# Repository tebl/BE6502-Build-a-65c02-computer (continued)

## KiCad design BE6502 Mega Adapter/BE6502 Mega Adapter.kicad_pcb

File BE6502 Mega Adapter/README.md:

[Ben Eater](https://eater.net/) has been a huge inspiration for many getting into building computers using basic electronic building blocks, his [videos](https://www.youtube.com/user/eaterbc) are truly excellent and it is no wonder he's often referred to as the Bob Ross of Breadboards! His latest project is [building a 6502 computer](https://eater.net/6502) on a breadboard, a video series that I'm sure will also inspire a lot of new users to the art of building stuff with the 6502! Check out the main [README](https://github.com/tebl/BE6502) for an overview of all the modules available to the BE6502 computer.

## Arduino Mega 2560-shield and Backplane
During the initial videos, Ben Eater shows how an Arduino Mega 2560 can be used when debugging or even seeking to understand how a 6502 computer works. This is done by connecting up the address/data busses as well as some of the control signals (R/W and the clock), the values are then printed every clock pulse.

That's a lot of wires and I don't have that kind of patience, so I designed it as an Arduino Mega 2560-shield that doubles up as a two (or three) slot backplane. You plug the SBC-module into one of them, then you can use the other for whatever expansion module you want to try out with the system. The third and outer set of pins can be installed as slot in the same manner, but I opted to install straight header pins here instead - that way I can use some female to male dupont wires and easily run them as needed over to a breadboard.

I've adapted the Arduino sketch created by Ben Eater, mostly I've just changed a few minor things to have them just like I would like them to be - I've also added all of the other BE6502-backplane signals available since they have all been mapped over to the Arduino Mega 2560. What's particularly awesome about that is that you can program the Arduino Mega to manually control the signalling without the SBC-module present, meaning that you now have the added ability to test out expansion module logic step by step.

For more information about using the sketch to analyze the computer while it is running as well as a few annotations that should help make the data streaming into the console more understandable, see [6502-monitor](https://github.com/tebl/BE6502/tree/master/software/arduino/6502-monitor) within the software-section of the project. Arduino console with the reset vector highlighted in yellow can be seen below as an example of output.

## Jumpers
| Reference | Position | Description                                        |
| --------- | -------- | -------------------------------------------------- |
| USB_PWR   | o-o *    | Link to power from/to Arduino Mega 2560            |

*) This is the default position and will allow the Arduino Mega 2560 to be powered at all times, so do not be alarmed if the module wakes up when power is applied to the BE6502 SBC barrel connector - remove jumper to keep it off if you're not running any sketches that work without a computer connected to the module.

# Schematic
The supplied KiCad files should be sufficient as both a schematic and as a starting point for ordering PCBs (basically you could just zip the contents of the export folder and upload that on a fabrication site), the schematic is also available in [PDF-format](https://github.com/tebl/BE6502/raw/master/BE6502%20Mega%20Adapter/export/BE6502%20Mega%20Adapter.pdf) so that you can refer to it while troubleshooting. You could even print it out and hang it on your office wall, excellent conversation starter at any technology-oriented business worth working at (or so I keep telling myself)!

# BOM
This is the part list as it stands now, most should be easy to get a hold of from your local electronic component shop though you might have to consider other sources depending on the quality of yourlocal vendor.

Some vendors will have the same ICs in different form factors, the ones you want will often be specified as being in the form of a DIP/PDIP package. Usually you'll want sockets for each of the ICs as well, a bag of assorted sockets should be easily available without setting you back more than a couple bucks. With the sockets in place, you don't need to dread having to remove an IC later, this leads to easier fault finding and you can easily "borrow" them for other projects later!

| Reference    | Item                                  | Count |
| ------------ | ------------------------------------- | ----- |
| PCB          | Fabricate yourself using Gerber files ([order](https://www.pcbway.com/project/shareproject/BE6502_Build_a_6502_computer__Arduino__and_backplane_module_.html?inviteid=88707)) |     1 |
| C1.C2,C3     | 100nF ceramic capacitor               |     3 |
| J1           | 39p straight pin header *             |     1 |
| J2-J3        | 39p female pin header *               |     2 |
| JP1          | 2p straight pin header                |     1 |
|              | Jumpers for settings (CAP headers)    |     1 |
| XA1          | Arduino pin headers **                |       |

*) You won't find the exact pin count for these, so the easiest is to use the 40 pin versions instead - either leave the last pin hangig across where pin 40 should have been or snip it off!

**) I'm not going to list these separatately, but you'll need some single and double row pin headers that you can cut down to size and solder to the board. Usually I insert them into the Mega itself, position the board on top and then tack each one in place temporarily to get the alignment correct. Remove the Arduino Mega 2560 board, then finally solder the pin headers into place.

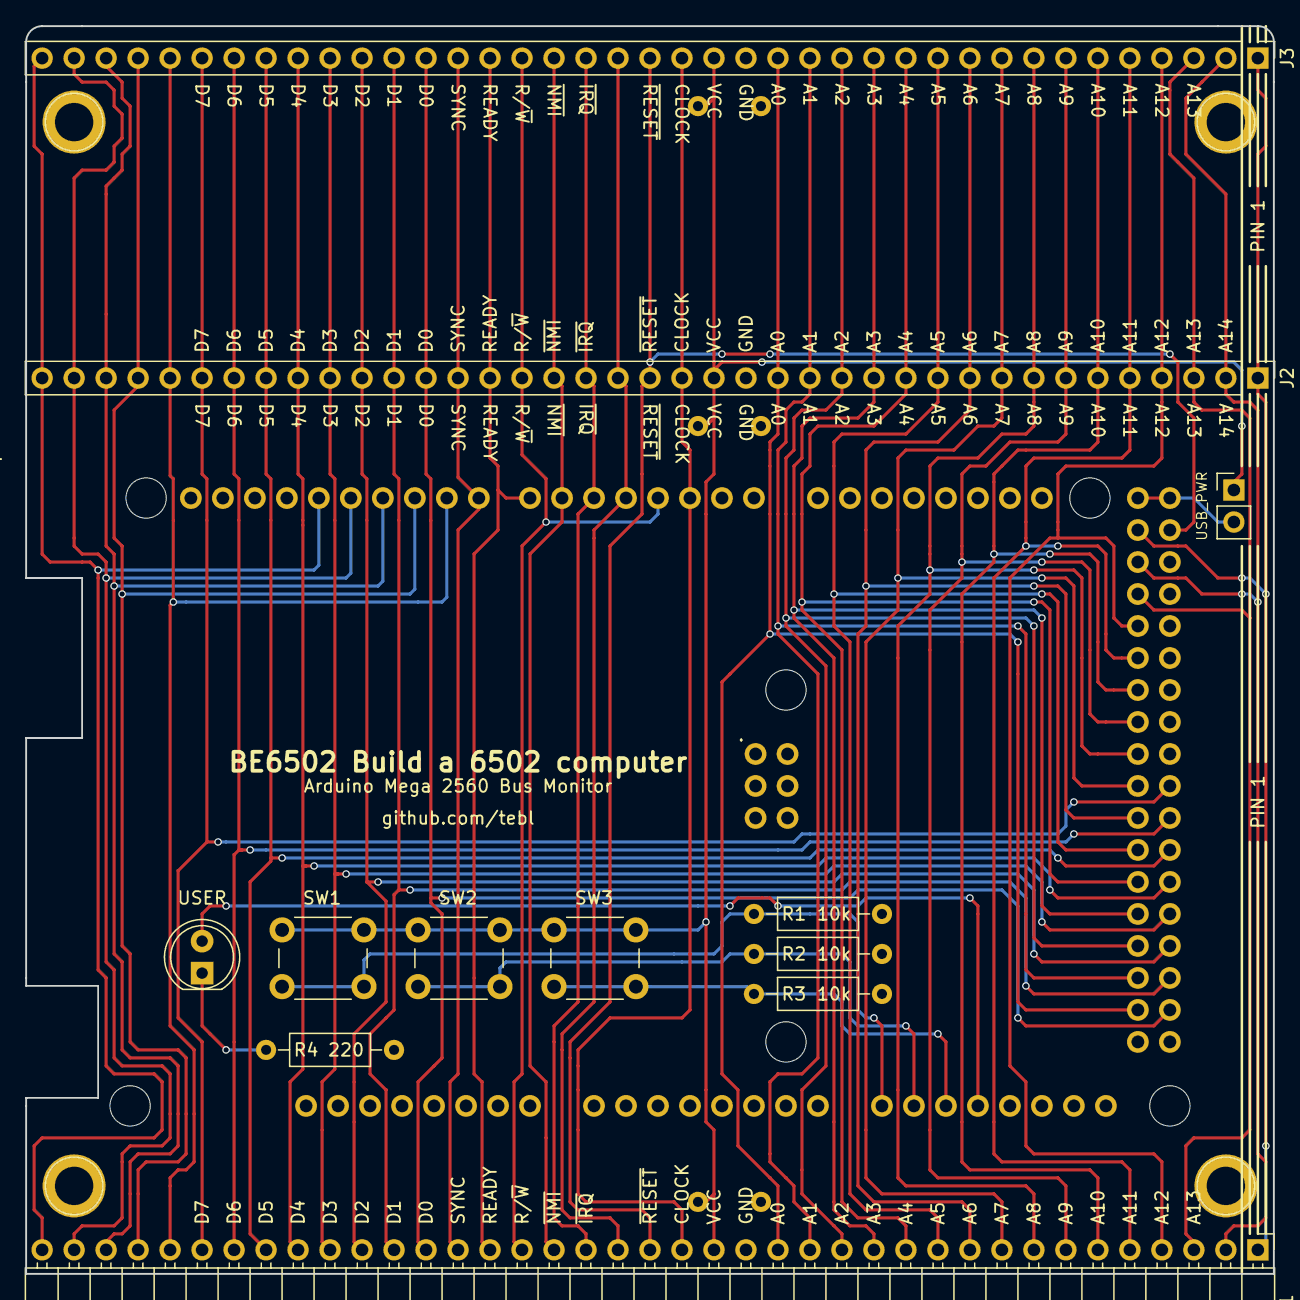
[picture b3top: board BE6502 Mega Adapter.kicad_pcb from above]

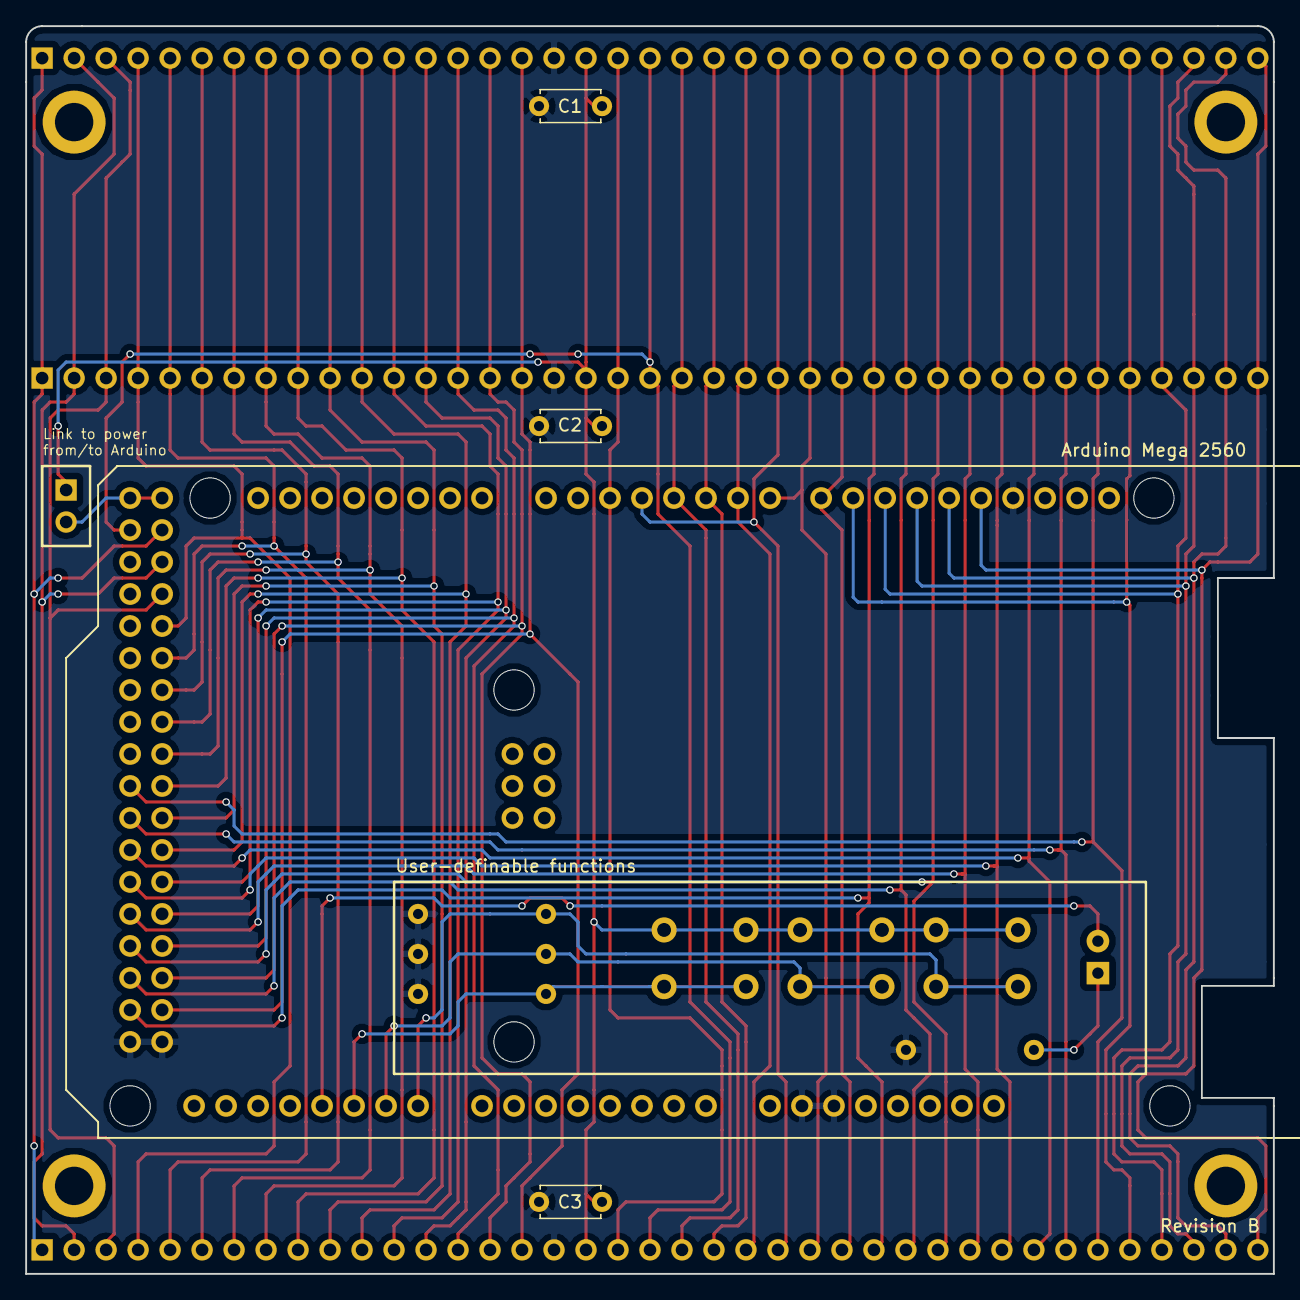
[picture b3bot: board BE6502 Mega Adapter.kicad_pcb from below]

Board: 2 copper layers, 99.1 x 99.1 mm, 20 parts (3 on the bottom side), 45 nets.

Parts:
C1, C2, C3: 100nF; C_Disc_D4.7mm_W2.5mm_P5.00mm
D1: USER; LED_D5.0mm
J1: Expansion; Pin_Header_Angled_1x39_Pitch2.54mm
J2: Slot #1; Pin_Header_Straight_1x39_Pitch2.54mm
J3: Slot #2; Pin_Header_Straight_1x39_Pitch2.54mm
JP1: USB_PWR; Pin_Header_Straight_1x02_Pitch2.54mm
M1, M2, M3, M4: Mounting; 1pin
R1, R2, R3: 10k; R_Axial_DIN0207_L6.3mm_D2.5mm_P10.16mm_Horizontal
R4: 220; R_Axial_DIN0207_L6.3mm_D2.5mm_P10.16mm_Horizontal
SW1, SW2, SW3: SW_Push; SW_PUSH_6mm
XA1: Arduino_Mega2560_Shield

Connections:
/A0: J1.16, J2.16, J3.16, XA1.D52
/A1: J1.15, J2.15, J3.15, XA1.D50
/A2: J1.14, J2.14, J3.14, XA1.D48
/A3: J1.13, J2.13, J3.13, XA1.D46
/A4: J1.12, J2.12, J3.12, XA1.D44
/A5: J1.11, J2.11, J3.11, XA1.D42
/A6: J1.10, J2.10, J3.10, XA1.D40
/A7: J1.9, J2.9, J3.9, XA1.D38
/A8: J1.8, J2.8, J3.8, XA1.D36
/A9: J1.7, J2.7, J3.7, XA1.D34
/A10: J1.6, J2.6, J3.6, XA1.D32
/A11: J1.5, J2.5, J3.5, XA1.D30
/A12: J1.4, J2.4, J3.4, XA1.D28
/A13: J1.3, J2.3, J3.3, XA1.D26
/A14: J1.2, J2.2, J3.2, XA1.D24
/A15: J1.1, J2.1, J3.1, XA1.D22
/CLOCK: J1.19, J2.19, J3.19, XA1.D2
/D0: J1.27, J2.27, J3.27, XA1.D53
/D1: J1.28, J2.28, J3.28, XA1.D51
/D2: J1.29, J2.29, J3.29, XA1.D49
/D3: J1.30, J2.30, J3.30, XA1.D47
/D4: J1.31, J2.31, J3.31, XA1.D45
/D5: J1.32, J2.32, J3.32, XA1.D43
/D6: J1.33, J2.33, J3.33, XA1.D41
/D7: J1.34, J2.34, J3.34, XA1.D39
/PIN21: J1.21, J2.21, J3.21, XA1.D4
/PIN35: J1.35, J2.35, J3.35, XA1.D9
/PIN36: J1.36, J2.36, J3.36, XA1.D10
/PIN37: J1.37, J2.37, J3.37, XA1.D11
/PIN38: J1.38, J2.38, J3.38, XA1.D12
/PIN39: J1.39, J2.39, J3.39, XA1.D13
/R/~W: J1.24, J2.24, J3.24, XA1.D3
/SYNC: J1.26, J2.26, J3.26, XA1.D8
/~IRQ: J1.22, J2.22, J3.22, XA1.D5
/~NMI: J1.23, J2.23, J3.23, XA1.D6
/~RDY: J1.25, J2.25, J3.25, XA1.D7
/~RESET: J1.20, J2.20, J3.20, XA1.D23
GND: C1.2, C2.2, C3.2, J1.17, J2.17, J3.17, R1.2, R2.2, R3.2, R4.2, XA1.GND1, XA1.GND2, XA1.GND3, XA1.GND5, XA1.GND6
unnamed: D1.1, R4.1
unnamed: D1.2, XA1.A11
unnamed: JP1.2, XA1.5V3, XA1.5V4
unnamed: R1.1, SW1.2, XA1.A8
unnamed: R2.1, SW2.2, XA1.A9
unnamed: R3.1, SW3.2, XA1.A10
VCC: C1.1, C2.1, C3.1, J1.18, J2.18, J3.18, JP1.1, SW1.1, SW2.1, SW3.1

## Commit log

2019-11-04 Schematic done
2019-11-04 Added LEDs
2019-11-04 Component placement
2019-11-07 Layout done
2019-11-13 Added PCB preview
2019-11-13 Added README and TODO
2019-11-13 Tweaked README
2019-11-13 Added SBC README
2019-11-16 Added clock module
2019-11-16 Updated gerbers for CPU
2019-11-17 Arduino bus monitor layout
2019-11-17 Added clock README
2019-11-17 Mega Adapter gerber export
2019-11-24 Simple blink programs
2019-11-27 Moved blink
2019-11-27 Copied Ben Eaters Arduino sketch
2019-11-27 Arduino monitor description
2019-11-27 Adjusted clock module after building
2019-11-27 Added pictures
2019-11-28 Adjusted SBC silkscreen
2019-11-28 Updated Mega shield silkscreen
2019-11-28 Updated backplane silkscreen
2019-11-28 Updated main README
2019-11-28 CPU README updated
2019-11-28 Updated clock README
2019-11-28 Arduino-module README added
2019-12-06 LCD example works!
2019-12-06 Output string
2019-12-06 Changed LCD message
2019-12-06 hello_lcd example
2019-12-06 Renamed examples
2019-12-06 Added LCD gallery image
2019-12-06 Updated 6502-monitor README to reflect examples being renamed
2019-12-07 Updated IC family note and TODO
2019-12-07 Example 002 and 003, currently untested and probably full of bugs
2019-12-07 Link to 6502 Primer added
2019-12-07 Updated example 003 listing
2019-12-07 Examples README
2019-12-08 Scratchpad example
2019-12-09 Scratchpad example runs at 1Mhz
2019-12-09 LCD image in README
2019-12-09 Updated examples README
2019-12-10 Started on notepad example
2019-12-10 LCD_POS works again
2019-12-11 Notepad can cycle characters
2019-12-11 Renamed example 005 to namebadge
2019-12-12 Character UP/DOWN with mode switch (untested)
2019-12-12 Handle moving left and right while in load mode
2019-12-13 Fixed DOWN in MODE=1
2019-12-13 UP/DOWN now count correctly
2019-12-14 LAST character works
2019-12-14 Clear first RAM byte, MODE correctly set on sideways move.
2019-12-14 Example 005 done (maybe, may be bugs)
2019-12-14 MiniPro images
2019-12-14 Updated example README
2019-12-14 Added memory map
2020-01-18 Added some switches and an LED to unused pins
2020-02-13 Images
2020-02-13 Updated Mega Adapter to Kicad 5
2020-02-13 PlatformIO project
2020-02-13 Defined all pins
2020-02-13 Moved on_clock
2020-02-13 Switch debouncing
2020-02-14 Fixed sketch compilation error
2020-02-14 Updated clock with capacitor from video 3
2020-02-14 Tweaks to schematic
2020-02-15 Added BE pin to backplane
2020-02-15 Backplane symbol updated
2020-02-15 Attempt to use timer3 as clock (untested)
2020-02-16 Tweaked Arduino clock functions
2020-02-17 Added picture
2020-02-17 Add errata
2020-02-17 Cosmetic schematic tweak
2020-02-17 ANSI status command
2020-02-18 Clear screen and add text decoration
2020-02-18 Hit period to do a tick
2020-02-18 Added current limiting resistor in case more than one clock accidentally activated at the same time
2020-02-18 Moved arduino clock and reset functions into separate file
2020-02-18 Can set clock speed directly
2020-02-19 Use bus enable to stop CPU and read memory directly
2020-02-20 Proxy switch actions through commands
2020-02-20 Function naming consistency
2020-02-20 Mode change takes control of bus
2020-02-21 ANSI overload functions for one-off commands
2020-02-21 Bus control issue fixed due to wrong sequence
2020-02-21 Shorten down code by using new formatting
2020-02-21 Fixed RAM test
2020-02-21 int is only 2 bytes, so use long
2020-02-21 Type in memory map
2020-02-22 Added limited dump commands
2020-02-22 Paper tape export added
2020-02-22 Read Intel HEX
2020-02-22 Moved help into separate files
2020-02-23 Arduino README tweaked
2020-03-11 Revised SBC to add reset circuit
2021-11-30 Fixed issue with clock module
2021-11-30 Update errata and bump module revision number
